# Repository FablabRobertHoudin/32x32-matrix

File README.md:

# Afficheur LED 32x32 disponible au Fablab

Base information: "RGB Panel Hookup Guide"
https://learn.sparkfun.com/tutorials/rgb-panel-hookup-guide

- Arduino sketch

ESP_32x32.ino 
Support affichage, connection internet en Wifi (2 réseau possible: perso / fablab par ex)
Recupère l'heure en NTP
Affiche les messages publiés par les utilisateurs (PubNub), grace à l'appli Android (APK)

- ESP-12e

Schéma disponible PDF
Attention à l'alimentation:
matrice en 5V (prise USB par ex)
ESP en 3.3V avec régulateur + condensateur 100µF.

http://esp8266.ru/esp8266-pin-register-strapping/

GPIO 0,2,4,5, 12-16 + 9-10 + 1,3 (USART)

GPIO9-10: 
http://smarpl.com/content/esp8266-esp-201-module-freeing-gpio9-and-gpio10

http://www.instructables.com/id/ARDUINO-SOLAR-CHARGE-CONTROLLER-Version-30/

- Application Android

Version très basique, APK dispo

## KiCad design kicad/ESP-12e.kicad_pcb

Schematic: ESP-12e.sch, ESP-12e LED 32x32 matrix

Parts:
K1: CONN_3
P1: 32x32 RGB panel
P2: RXTX
P3: Alim 3.3V
R1: 10k
SW2: Reflash
U1: ESP-12E
U3: 4040

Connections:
+3.3V: K1.1, P3.1, U1.3, U1.8, U3.16 (VDD)
A: P1.9, U3.9 (Q0)
B: P1.10, U3.7 (Q1)
B0: P1.3, SW2.1, U1.18
B1: P1.7, P2.2 (PM), U1.21
C: P1.11, U3.6 (Q2)
CLK: P1.13, U1.5
D: P1.12, U3.5 (Q3)
G0: P1.2, U1.17
G1: P1.6, U1.20
GND: K1.3, P1.4, P1.8, P1.16, P3.2 (PM), R1.2, SW2.2, U1.15, U3.8 (VSS)
unnamed: P2.1, U1.22
unnamed: U3.3 (Q4), U3.11 (Reset)
unnamed: K1.2 (PM), U1.2
unnamed: U1.7, U3.10 (CLK)
OE: P1.15, U1.6
R0: P1.1, R1.1, U1.16
R1: P1.5, U1.19
STB: P1.14, U1.4

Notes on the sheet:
18 GPIO0 (f1) reflash si Gnd 22 GPIO1 (f4) U0TX (f1) 17 GPIO2 (f1) U1TX (f3) U0TX (f5) 21 GPIO3 (f4) U0RX (f1) 19 GPIO4 20 GPIO5 GPIO6 ? GPIO7 ? GPIO8 ? 11 GPIO9 ? 12 GPIO10 ? GPIO11 ? 6 GPIO12 7 GPIO13 5 GPIO14 16 GPIO15 4 GPIO16 2 GPIO17 ADC

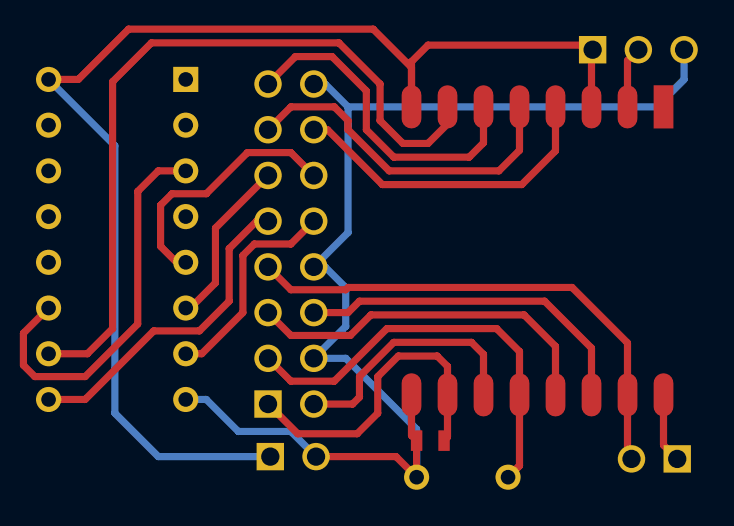
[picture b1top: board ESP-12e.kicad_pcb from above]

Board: 2 copper layers, 8 parts (0 on the bottom side), 19 nets.

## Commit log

2015-06-09 :octocat: Added .gitattributes
2015-06-09 Creation
    description & initial Arduino sketch
2015-06-09 Affichage "Fablab Robert-Houdin"
    Version Arduino Uno "Fablab Robert-Houdin"
    Dispo au 1 juin 2015
2015-06-09 directory change
    déplacement sketch dans répertoire
2015-07-10 First working test
    Added Kicad schema
    Arduino ESP test
2015-10-30 Working version
    - Correction de code (fonctionnel)
    - Schéma circuit
    - Application Android (APK, version de base)
